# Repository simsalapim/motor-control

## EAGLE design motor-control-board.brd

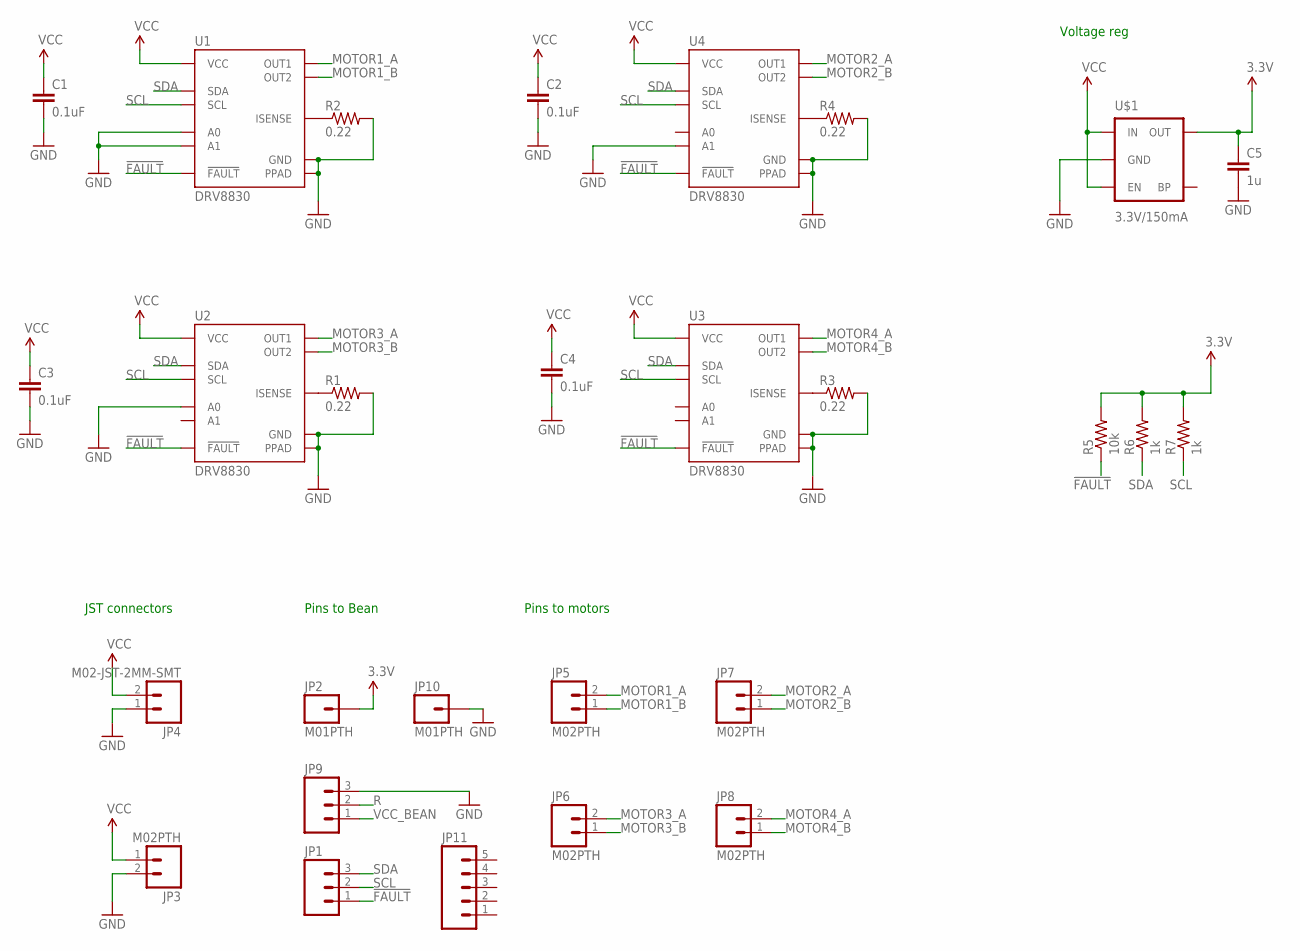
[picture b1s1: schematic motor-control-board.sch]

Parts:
C1, C2, C3, C4: 0.1uF; 0402-CAP
C5: 1u; 0402-CAP
JP1, JP9: M03PTH; 1X03
JP2, JP10: M01PTH; 1X01
JP3, JP5, JP6, JP7, JP8: M02PTH; 1X02
JP4: M02-JST-2MM-SMT; JST-2-SMD
JP11: M05PTH; 1X05
R1, R2, R3, R4: 0.22; 0805
R5: 10k; 0402-RES
R6, R7: 1k; 0402-RES
U1, U2, U3, U4: DRV8830; MSOP-10-GNDPAD
U$1: 3.3V/150mA; SOT23-5

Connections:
3.3V: C5.1, JP2.1, R5.2, R6.2, R7.2, U$1.5 (OUT)
!FAULT: JP1.1, R5.1, U1.6 (!FAULT), U2.6 (!FAULT), U3.6 (!FAULT), U4.6 (!FAULT)
GND: C1.2, C2.2, C3.2, C4.2, C5.2, JP3.2, JP4.1 (2), JP9.3, JP10.1, R1.2, R2.2, R3.2, R4.2, U1.5 (GND), U1.7 (A0), U1.8 (A1), U1.GND (PPAD), U2.5 (GND), U2.7 (A0), U2.GND (PPAD), U3.5 (GND), U3.GND (PPAD), U4.5 (GND), U4.8 (A1), U4.GND (PPAD), U$1.2 (GND)
MOTOR1_A: JP5.2, U1.3 (OUT1)
MOTOR1_B: JP5.1, U1.1 (OUT2)
MOTOR2_A: JP7.2, U4.3 (OUT1)
MOTOR2_B: JP7.1, U4.1 (OUT2)
MOTOR3_A: JP6.2, U2.3 (OUT1)
MOTOR3_B: JP6.1, U2.1 (OUT2)
MOTOR4_A: JP8.2, U3.3 (OUT1)
MOTOR4_B: JP8.1, U3.1 (OUT2)
unnamed: R2.1, U1.2 (ISENSE)
unnamed: R3.1, U3.2 (ISENSE)
unnamed: R1.1, U2.2 (ISENSE)
unnamed: R4.1, U4.2 (ISENSE)
R: JP9.2
SCL: JP1.2, R7.1, U1.10 (SCL), U2.10 (SCL), U3.10 (SCL), U4.10 (SCL)
SDA: JP1.3, R6.1, U1.9 (SDA), U2.9 (SDA), U3.9 (SDA), U4.9 (SDA)
VCC: C1.1, C2.1, C3.1, C4.1, JP3.1, JP4.2 (1), U1.4 (VCC), U2.4 (VCC), U3.4 (VCC), U4.4 (VCC), U$1.1 (IN), U$1.3 (EN)
VCC_BEAN: JP9.1

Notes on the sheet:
Voltage reg
JST connectors
Pins to Bean
Pins to motors

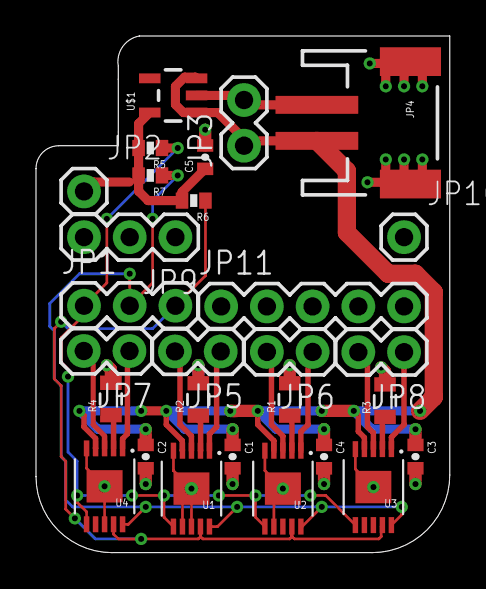
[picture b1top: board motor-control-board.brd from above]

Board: 2 copper layers, 23.0 x 28.7 mm, 28 parts (0 on the bottom side), 18 nets.

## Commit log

2015-02-12 prior to making bigger board
2015-02-13 Before adding 0805 resistors

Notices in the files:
parts and their libraries:
SparkFun-Capacitors: Licensing: Creative Commons ShareAlike 4.0 International - https://creativecommons.org/licenses/by-sa/4.0
